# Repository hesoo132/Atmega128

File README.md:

# ATmega128A Security System Board

> Keypad + LCD + Bluetooth(HC‑06) + Shock Sensor(SW‑420) + Servo Lock + Buzzer
> Education & Smart Access Control Prototyping Platform

---

## 🔎 Overview
The **ATmega128A Security System Board** is a compact AVR platform for **learning, prototyping, and access‑control demos**.
It integrates **12 V → 5 V/3.3 V** power, **USB‑UART**, **ISP programming**, **keypad+LCD UI**, **HC‑06 Bluetooth**, **SW‑420 vibration detection**, **servo lock**, and **buzzer alerts**.

---

## 📸 PCB Overview
| Top View | Bottom View |
|----------|-------------|
|  |  |

> Schematics (PNG): 

---

## 📑 Design Resources
- **MCU**: ATmega128A‑AU (8‑bit AVR)
- **EDA**: KiCad 9.0.x
- **Board**: 2‑layer

---

## ⚙️ Key Hardware Notes
- **Power**: 12 V barrel jack → **TPS562201‑5.0 / TPS562201‑3.3** rails
- **Clock**: 16 MHz crystal
- **Programming**: **ISP header** (AVRDUDE/USBasp/Atmel‑ICE)
- **USB‑UART**: FT232RL (debug console / host comms)
- **UI/Peripherals**:
  - **Keypad (J5)**: enter/change password
  - **LCD (J4)**: show result/tries/lockout timer
  - **Servo**: unlock on success; stay locked on failure
  - **Buzzer**: success/fail tone + vibration alarm
  - **SW‑420 (J1)**: shock/vibration tamper detection
  - **HC‑06 (J2)**: Bluetooth data exchange

---

## 🔐 Security‑Oriented Features
| Module | Role |
|---|---|
| **Keypad (J5)** | Password entry / change |
| **LCD (J4)** | Status, error, lockout seconds |
| **Servo** | Door actuation (open on correct PIN) |
| **Buzzer** | Wrong PIN & vibration alarm |
| **SW‑420** | Tamper/shock detection |
| **HC‑06** | Remote monitor & control (UART over BT) |

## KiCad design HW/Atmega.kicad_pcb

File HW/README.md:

# ATmega128A Development Board

## 🔎 Overview
The **ATmega128A Development Board** is a versatile embedded platform for **AVR microcontroller learning, prototyping, and embedded system design**.  
It integrates stable power delivery, multiple communication interfaces, keypad & LCD modules, and expansion connectors for external devices.

---

## 📸 PCB Overview
| Top View | Bottom View |
|----------|-------------|
|  |  |

---

## 📑 Design Resources
- **Schematics**: [Atmega.pdf](Atmega.pdf) (KiCad 9.0.4)

---

## 🔧 Key Hardware Notes
- **EDA Tool**: KiCad 9.0.4  
- **PCB Stackup**: 2-layer standard  
- **MCU**: ATmega128A-AU (8-bit AVR, Ports A–G exposed)  
- **Power**: 12 V input → 5 V & 3.3 V rails (TPS562201 regulators)  
- **Interfaces**: USB-to-Serial (FT232RL), ISP programmer header  
- **User IO**: Keypad, LCD, Servo motor, Buzzer, LEDs  
- **Sensors**: SW-420 vibration/shock sensor  
- **Communication**: HC-06 Bluetooth module

---

## 🧩 Schematic Highlights

### 1) MCU — ATmega128A-AU  
- **Role**: Central controller for all peripherals  
- **Features**: GPIO Ports A–G, external 16 MHz crystal, reset circuit  
- **Purpose**: Main processing unit for password and control logic

---

### 2) Power
- **Input**: Barrel Jack (12 V)  
- **Regulators**: TPS562201-5.0 & TPS562201-3.3  
- **Purpose**: Stable dual-voltage supply for mixed 5 V / 3.3 V peripherals

---

### 3) Communication 
- **USB-to-Serial**: FT232RL for PC connection & firmware upload  
- **ISP**: 6-pin header for direct programming  
- **Bluetooth (J2)**: HC-06 for wireless communication

---

### 4) User I/O
- **Keypad (J5)**: Password input & modification  
- **LCD (J4)**: Password confirmation, error display, lockout countdown  
- **LEDs (D1–D4)**: Status indicators  
- **Buzzer**: Alarm on wrong password or vibration detection  
- **Servo Motor**: Unlocks on correct password; locked otherwise  
- **SW-420 Sensor (J1)**: Detects vibration/shock for tamper alert

---

## ✅ Progress
- [x] Schematics completed  
- [x] PCB fabricated  
- [x] Power supply tested (5 V / 3.3 V OK)  
- [x] USB-Serial & ISP programming validated  
- [x] Keypad & LCD integrated  
- [x] Bluetooth bring-up (HC-06)  
- [x] Security application firmware in progress

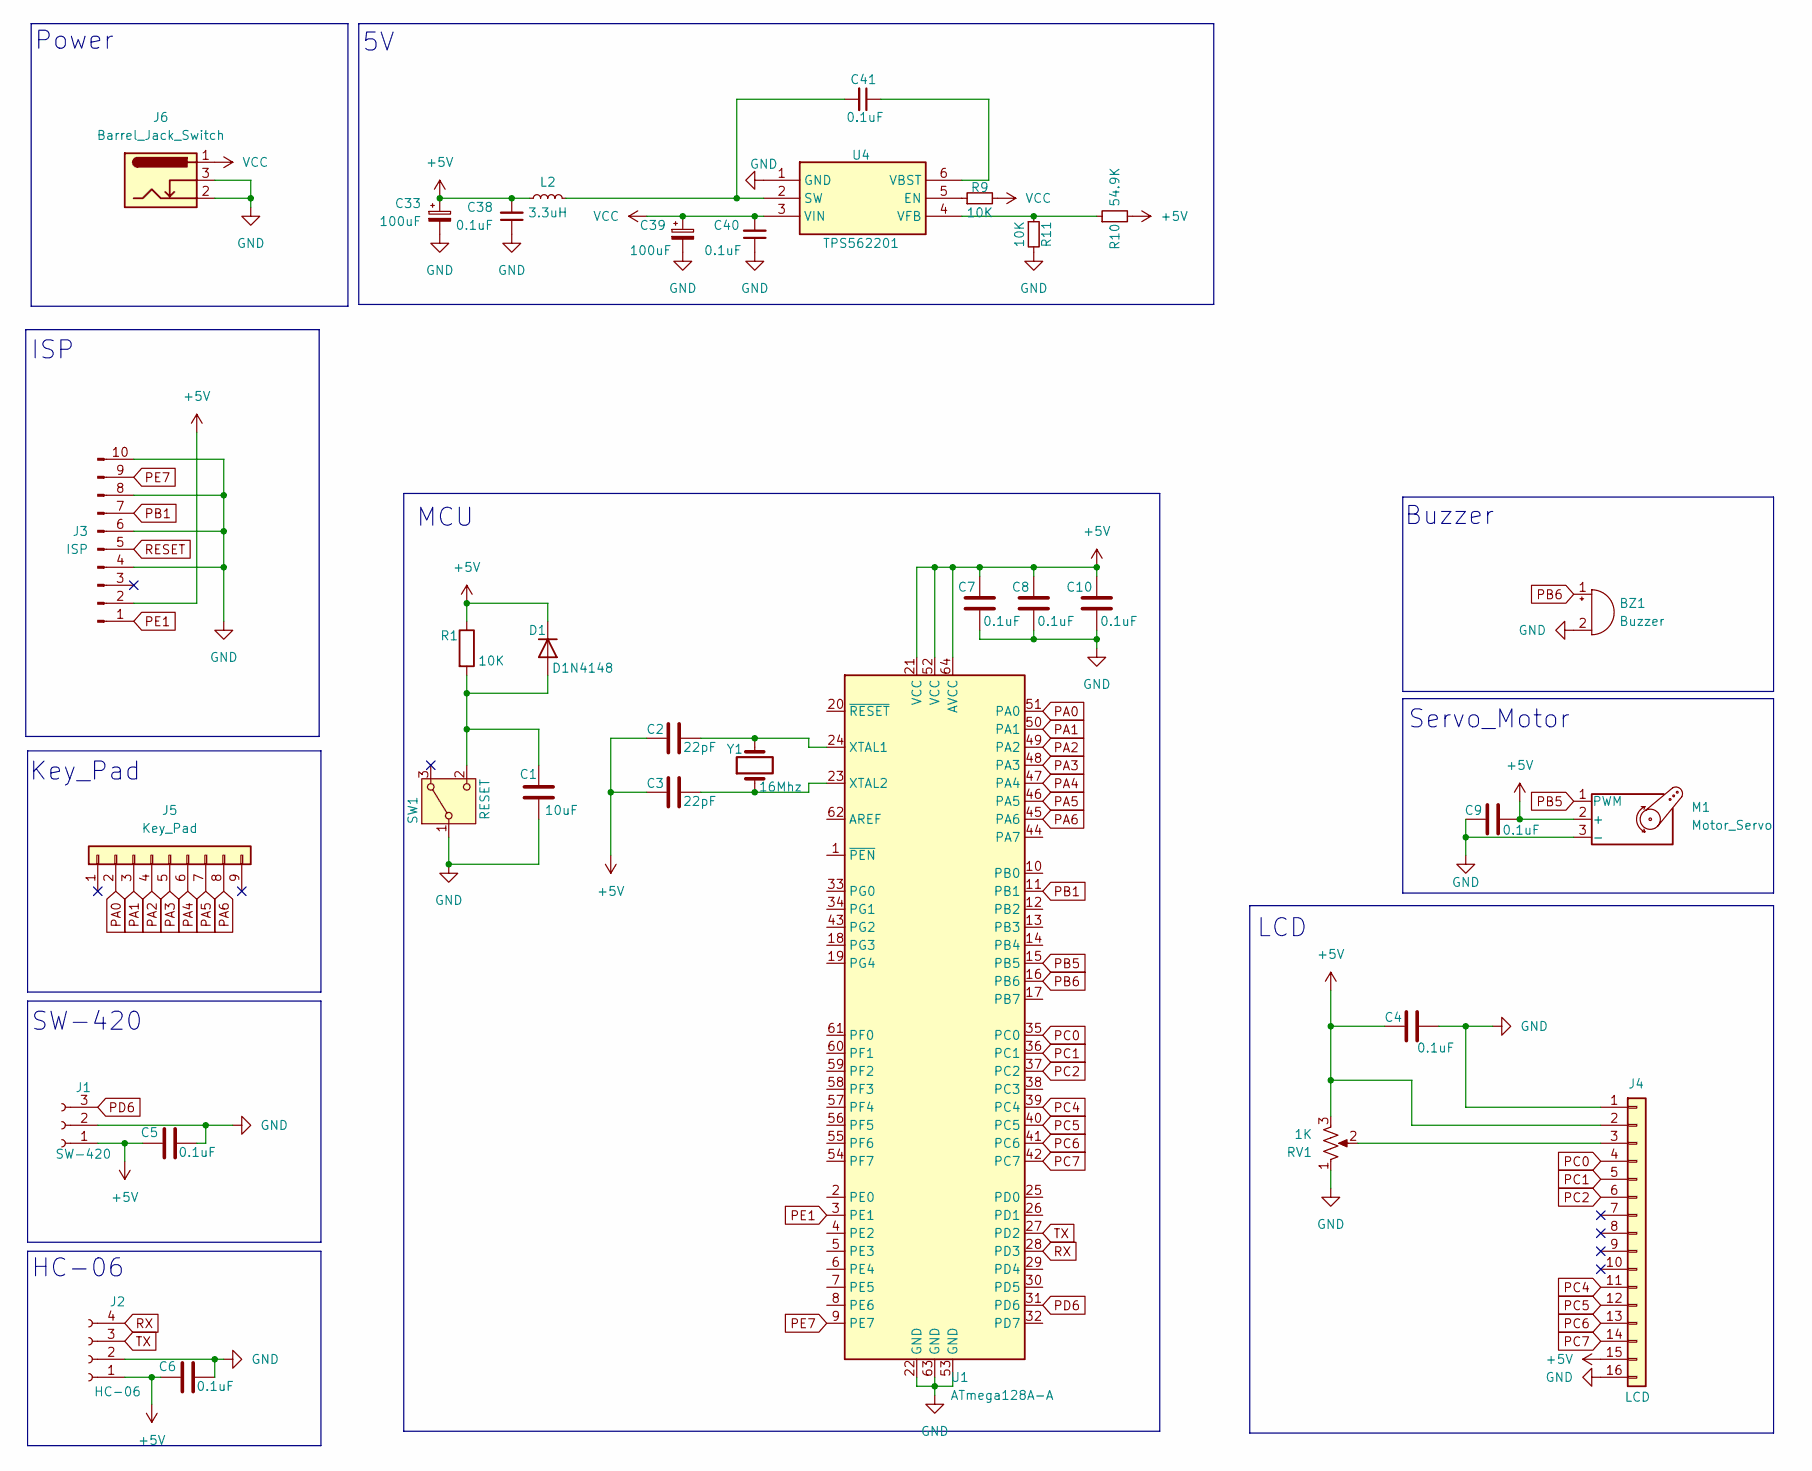
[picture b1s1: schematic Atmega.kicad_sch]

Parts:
BZ1: Buzzer; Buzzer_12x9.5RM7.6
C1: 10uF; C_0805_2012Metric
C2, C3: 22pF; C_0805_2012Metric
C4, C5, C6, C7, C8, C9, C10, C38, C40, C41: 0.1uF; C_0805_2012Metric
C33, C39: 100uF; CP_Elec_6.3x5.9
D1: D1N4148; D_0805_2012Metric
J1: SW-420; PinHeader_1x03_P2.54mm_Vertical
J2: HC-06; PinHeader_1x04_P2.54mm_Vertical
J3: ISP; SHDR10W64P254_2X5_2036X885X925P
J4: LCD; PinHeader_1x16_P2.54mm_Vertical
J5: Key_Pad; PinHeader_1x09_P2.54mm_Vertical
J6: Barrel_Jack_Switch; BarrelJack_GCT_DCJ200-10-A_Horizontal
L2: 3.3uH; L_0805_2012Metric
M1: Motor_Servo; PinHeader_1x03_P2.54mm_Vertical
R1, R9, R11: 10K; R_0805_2012Metric
R10: 54.9K; R_0805_2012Metric
RV1: 1K; Potentiometer_Bourns_3386F_Vertical
SW1: RESET; TLSMDT3C020GLFS
U1: ATmega128A-A; TQFP-64_14x14mm_P0.8mm
U4: TPS562201; SOT-23-6; Mouser Part Number 595-TPS562201DDCR
Y1: 16Mhz; Crystal_HC52-6mm_Vertical

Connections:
+5V: C2.1, C3.1, C4.1, C5.1, C6.1, C7.2, C8.2, C9.1, C10.2, C33.1, C38.2, D1.1 (K), J1.1, J2.1, J3.2, J4.2, J4.15, L2.2, M1.2 (+), R1.1, R10.2, RV1.3, U1.21 (VCC), U1.52 (VCC), U1.64 (AVCC)
GND: BZ1.2 (-), C1.2, C4.2, C5.2, C6.2, C7.1, C8.1, C9.2, C10.1, C33.2, C38.1, C39.2, C40.1, J1.2, J2.2, J3.4, J3.6, J3.8, J3.10, J4.1, J4.16, J6.2, J6.3, M1.3 (-), R11.2, RV1.1, SW1.1 (B), U1.22 (GND), U1.53 (GND), U1.63 (GND), U4.1 (GND)
unnamed: C1.1, D1.2 (A), R1.2, SW1.2 (C)
unnamed: J4.3, RV1.2
unnamed: C2.2, U1.24 (XTAL1), Y1.2
unnamed: C3.2, U1.23 (XTAL2), Y1.1
unnamed: R9.1, U4.5 (EN)
unnamed: C41.2, L2.1, U4.2 (SW)
unnamed: C41.1, U4.6 (VBST)
unnamed: R10.1, R11.1, U4.4 (VFB)
PA0: J5.2, U1.51 (PA0)
PA1: J5.3, U1.50 (PA1)
PA2: J5.4, U1.49 (PA2)
PA3: J5.5, U1.48 (PA3)
PA4: J5.6, U1.47 (PA4)
PA5: J5.7, U1.46 (PA5)
PA6: J5.8, U1.45 (PA6)
PB1: J3.7, U1.11 (PB1)
PB5: M1.1 (PWM), U1.15 (PB5)
PB6: BZ1.1 (+), U1.16 (PB6)
PC0: J4.4, U1.35 (PC0)
PC1: J4.5, U1.36 (PC1)
PC2: J4.6, U1.37 (PC2)
PC4: J4.11, U1.39 (PC4)
PC5: J4.12, U1.40 (PC5)
PC6: J4.13, U1.41 (PC6)
PC7: J4.14, U1.42 (PC7)
PD6: J1.3, U1.31 (PD6)
PE1: J3.1, U1.3 (PE1)
PE7: J3.9, U1.9 (PE7)
RESET: J3.5
RX: J2.4, U1.28 (PD3)
TX: J2.3, U1.27 (PD2)
VCC: C39.1, C40.2, J6.1, R9.2, U4.3 (VIN)

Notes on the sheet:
Buzzer
ISP
HC-06
Servo_Motor
LCD
Power
MCU
SW-420
Key_Pad

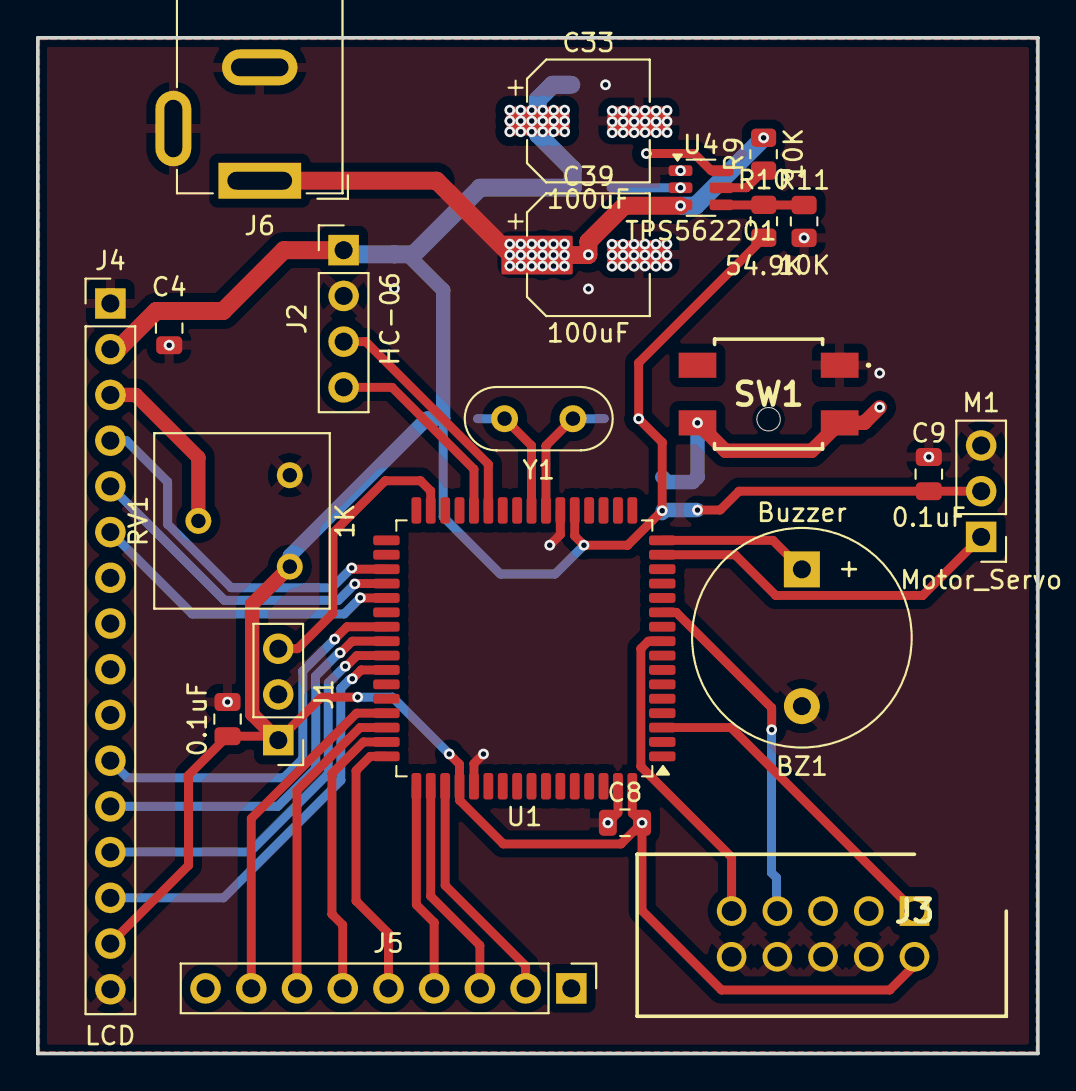
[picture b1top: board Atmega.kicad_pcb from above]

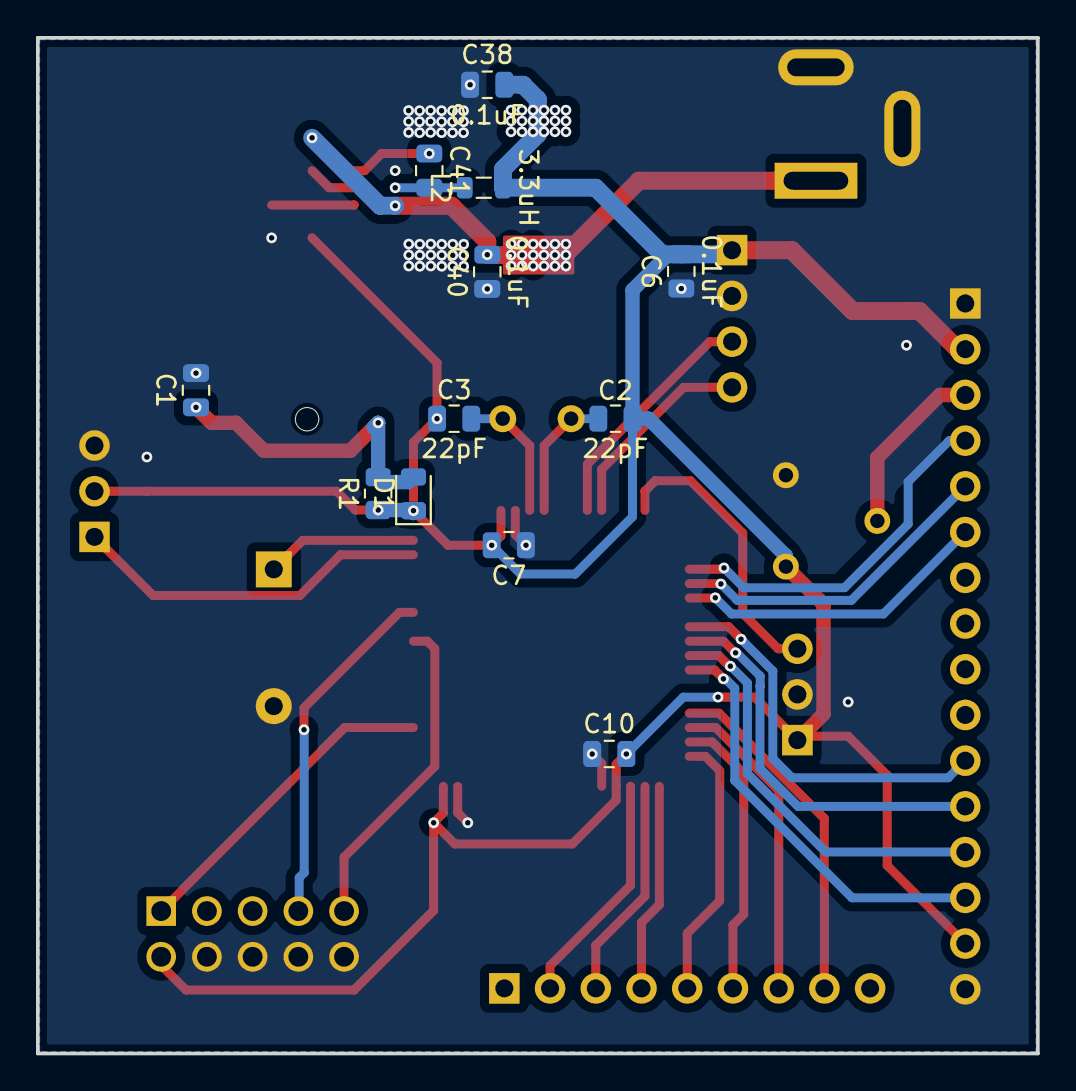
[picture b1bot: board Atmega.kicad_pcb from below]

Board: 2 copper layers, 55.6 x 56.4 mm, 34 parts (12 on the bottom side), 33 nets.
